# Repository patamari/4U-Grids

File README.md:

# 4U-Grids
4U port of MI Grids, Topographic Drum Sequencer

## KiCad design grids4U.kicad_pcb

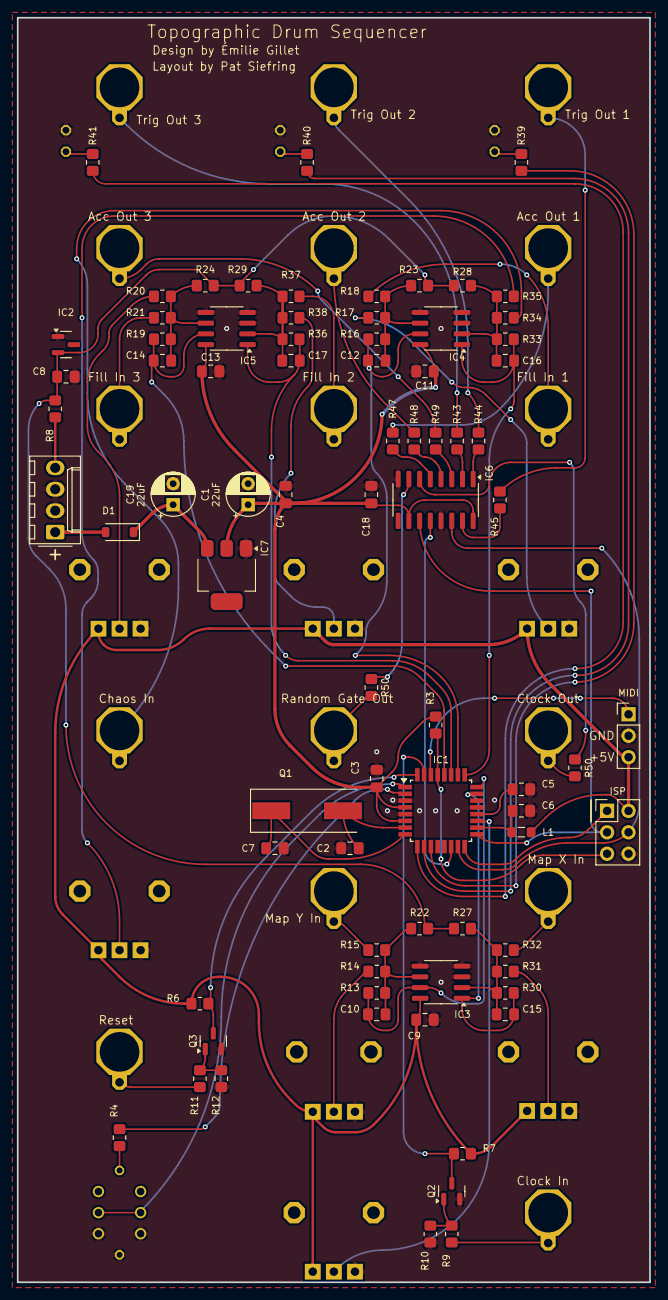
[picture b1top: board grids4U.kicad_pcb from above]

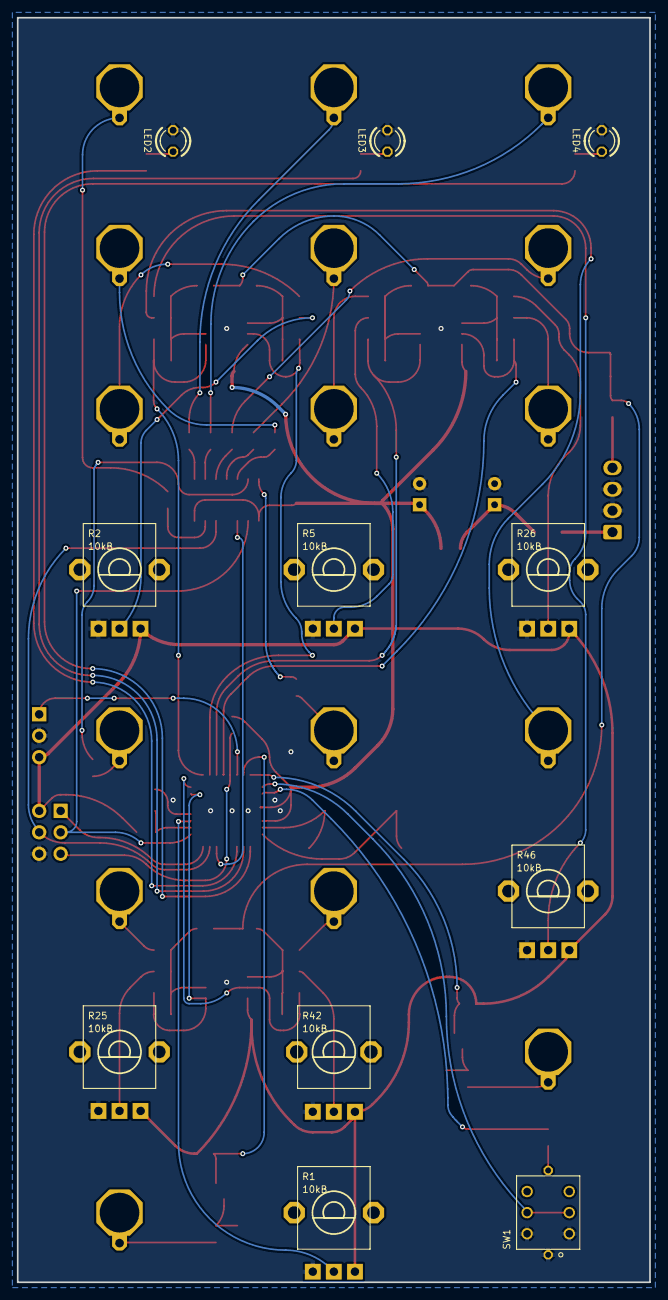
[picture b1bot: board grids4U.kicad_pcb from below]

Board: 2 copper layers, 74.9 x 149.9 mm, 88 parts (11 on the bottom side), 54 nets.

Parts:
C1, C19: 22uF; CP_Radial_D5.0mm_P2.50mm
C2, C7: 18p; C_0805_2012Metric_Pad1.18x1.45mm_HandSolder
C3, C4, C5, C6, C9, C11, C13, C18: 100n; C_0805_2012Metric_Pad1.18x1.45mm_HandSolder
C8: 470n; C_0805_2012Metric_Pad1.18x1.45mm_HandSolder
C10, C12, C14, C15, C16, C17: 10n; C_0805_2012Metric_Pad1.18x1.45mm_HandSolder
D1: 1N5819HW; D_SOD-123
IC1: ATMEGA328P-AU; TQFP-32_7x7mm_P0.8mm
IC2: LM4040 5.0V; SOT-23
IC3, IC4, IC5: MCP6002; SOIC-8_3.9x4.9mm_P1.27mm
IC6: 74HC595D; SOIC-16_3.9x9.9mm_P1.27mm
IC7: LM1117-5.0; SOT-223
ISP: PinHeader_2x03_P2.54mm_Vertical
L1: L_0805_2012Metric_Pad1.05x1.20mm_HandSolder
LED2, LED3, LED4: LED3MM
MIDI: PinHeader_1x03_P2.54mm_Vertical
Q1: 20MHz; Crystal_SMD_HC49-SD
Q2, Q3: MMBT3904; SOT-23
R1, R2, R5, R25, R26, R46: 10kB; ALPS_POT_VERTICAL_PS
R3, R6, R7, R8: 10k; R_0805_2012Metric_Pad1.20x1.40mm_HandSolder
R4, R39, R40, R41: 100; R_0805_2012Metric_Pad1.20x1.40mm_HandSolder
R9, R11, R13, R14, R15, R16, R17, R18, R19, R20, R21, R22, R23, R24, R27, R28, R29, R30, R31, R32, R33, R34, R35, R36, R37, R38: 100k; R_0805_2012Metric_Pad1.20x1.40mm_HandSolder
R10, R12: 1M; R_0805_2012Metric_Pad1.20x1.40mm_HandSolder
R42: 10kB; ALPS_POT_VERTICAL_PS4
R43, R44, R45, R47, R48, R49, R50, R50#2: 1.0k; R_0805_2012Metric_Pad1.20x1.40mm_HandSolder
SW1: LP4OA1PBCT

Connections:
+5V: C1.1, C3.1, C4.1, C9.1, C11.1, C13.1, C18.1, IC1.4, IC1.6, IC3.8, IC4.8, IC5.8, IC6.10, IC6.16, IC7.2, ISP.2, L1.1, MIDI.3, R1.P$1, R2.P$1, R3.2, R5.P$1, R6.2, R7.2, R25.P$1, R26.P$1, R42.P$1, R46.P$1
AREF: C5.1, IC1.20
CH1_CV: C12.2, IC1.26, IC4.7, R16.2
CH2_CV: C17.2, IC1.27, IC5.1, R36.2
CH3_CV: C14.2, IC1.28, IC5.7, R19.2
CLOCKOUTPRERESISTOR: IC6.6, R50.1
GATE1_LED: R4.2, SW1.L1
GATE2_LED: LED4.A, R41.2
GATE3_LED: LED3.A, R40.2
GATE4_LED: LED2.A, R39.2
GND: C1.2, C2.1, C3.2, C4.2, C5.2, C6.2, C7.1, C8.2, C9.2, C11.2, C13.2, C18.2, C19.2, IC1.3, IC1.5, IC1.21, IC2.1, IC3.3, IC3.4, IC3.5, IC4.3, IC4.4, IC4.5, IC5.3, IC5.4, IC5.5, IC6.8, IC6.13, IC7.1, ISP.6, LED2.K, LED3.K, LED4.K, MIDI.2, Q2.2, Q3.2, R1.P$3, R2.P$3, R5.P$3, R10.1, R12.1, R25.P$3, R26.P$3, R42.P$3, R46.P$3, SW1.L2, SW1.P3, SW1.P6
IN_CLOCK: IC1.31, Q2.3, R7.1
IN_MIDI: IC1.30, MIDI.1
IN_RESET: IC1.32, Q3.3, R6.1
LED_CH1: IC1.11, R39.1
LED_CH2: IC1.10, R40.1
LED_CH3: IC1.9, R41.1
LED_CLOCK: IC1.2, R4.1
MISO: IC1.16, ISP.1
MOSI: IC1.15, IC6.14, ISP.4
unnamed: Q2.1, R9.1, R10.2
unnamed: Q3.1, R11.1, R12.2
unnamed: R25.P$2, R31.1
unnamed: C10.1, IC3.6, R13.1, R14.2, R15.2, R22.2
unnamed: R14.1, R42.P$2
unnamed: C16.1, IC4.2, R28.2, R33.1, R34.2, R35.2
unnamed: R35.1, R46.P$2
unnamed: C12.1, IC4.6, R16.1, R17.2, R18.2, R23.2
unnamed: R2.P$2, R17.1
unnamed: C17.1, IC5.2, R29.2, R36.1, R37.2, R38.2
unnamed: R5.P$2, R38.1
unnamed: C14.1, IC5.6, R19.1, R20.2, R21.2, R24.2
unnamed: R20.1, R26.P$2
unnamed: IC6.15, R45.1
unnamed: IC6.1, R44.1
unnamed: C15.1, IC3.2, R27.2, R30.1, R31.2, R32.2
unnamed: IC6.2, R43.1
unnamed: IC6.3, R49.1
unnamed: IC6.4, R48.1
unnamed: IC6.5, R47.1
unnamed: C6.1, IC1.18, L1.2
unnamed: C7.2, IC1.8, Q1.1
unnamed: C2.2, IC1.7, Q1.2
RANDOMGATEPRERESISTOR: IC6.7, R50#2.1
REF_-5: C8.1, IC2.2, R8.2, R22.1, R23.1, R24.1, R27.1, R28.1, R29.1
RESET: IC1.29, ISP.5, R3.1
RND_CV: C16.2, IC1.25, IC4.1, R33.2
SCK: IC1.17, IC6.11, ISP.3
SS: IC1.14, IC6.12
SW_RESET: IC1.1, SW1.P2, SW1.P5
TEMPO: IC1.19, R1.P$2
VCC: C19.1, D1.1, IC7.3
X_CV: C15.2, IC1.23, IC3.1, R30.2
Y_CV: C10.2, IC1.24, IC3.7, R13.2
